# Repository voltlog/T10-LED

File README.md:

# T10-LED
T10 Automotive LED bulb, based on Cree LEDs and a constant current driver

More info about this project in [Voltlog #319](https://www.youtube.com/watch?v=uEePdwpdCJc).
You can also check out the C5W LED bulb project in [Voltlog #333](https://youtu.be/id2jNSogrME).

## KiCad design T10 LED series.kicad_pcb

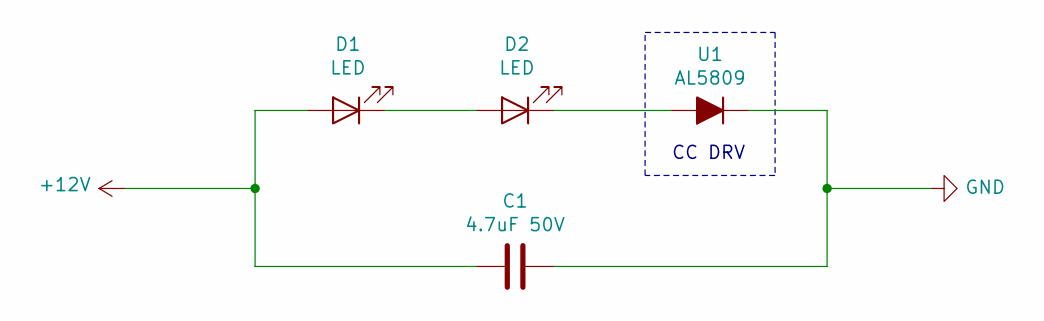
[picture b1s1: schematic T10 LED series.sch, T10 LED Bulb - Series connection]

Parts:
C1: 4.7uF 50V; C_1206_3216Metric; Part Number GCJ31CC71H475KA01L
D1, D2: LED; LED_PLCC_2835
U1: AL5809; D_PowerDI-123

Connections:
+12V: C1.1, D1.2 (A)
GND: C1.2, U1.1 (K)
unnamed: D1.1 (K), D2.2 (A)
unnamed: D2.1 (K), U1.2 (A)

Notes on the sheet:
CC DRV

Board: 2 copper layers, 4 parts (2 on the bottom side), 4 nets, no tracks yet.

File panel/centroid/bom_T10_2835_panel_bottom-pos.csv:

Ref,Val,Package,PosX,PosY,Rot,Side
"D2","LED","LED_PLCC_2835",109.150000,-54.400000,270.000000,bottom
"D2","LED","LED_PLCC_2835",96.250000,-81.400000,270.000000,bottom
"D2","LED","LED_PLCC_2835",134.950000,-81.400000,270.000000,bottom
"D2","LED","LED_PLCC_2835",147.850000,-81.400000,270.000000,bottom
"D2","LED","LED_PLCC_2835",160.750000,-81.400000,270.000000,bottom
"D2","LED","LED_PLCC_2835",173.650000,-81.400000,270.000000,bottom
"D2","LED","LED_PLCC_2835",109.150000,-81.400000,270.000000,bottom
"D2","LED","LED_PLCC_2835",122.050000,-81.400000,270.000000,bottom
"D2","LED","LED_PLCC_2835",173.650000,-54.400000,270.000000,bottom
"D2","LED","LED_PLCC_2835",160.750000,-54.400000,270.000000,bottom
"D2","LED","LED_PLCC_2835",147.850000,-54.400000,270.000000,bottom
"D2","LED","LED_PLCC_2835",134.950000,-54.400000,270.000000,bottom
"D2","LED","LED_PLCC_2835",122.050000,-54.400000,270.000000,bottom
"D2","LED","LED_PLCC_2835",96.250000,-108.400000,270.000000,bottom
"D2","LED","LED_PLCC_2835",160.750000,-108.400000,270.000000,bottom
"D2","LED","LED_PLCC_2835",147.850000,-108.400000,270.000000,bottom
"D2","LED","LED_PLCC_2835",173.650000,-108.400000,270.000000,bottom
"D2","LED","LED_PLCC_2835",109.150000,-108.400000,270.000000,bottom
"D2","LED","LED_PLCC_2835",122.050000,-108.400000,270.000000,bottom
"D2","LED","LED_PLCC_2835",134.950000,-108.400000,270.000000,bottom
"D2","LED","LED_PLCC_2835",96.250000,-54.400000,270.000000,bottom
"REF**","Fiducial_0.75mm_Mask1.5mm","Fiducial_0.75mm_Mask1.5mm",171.000000,-133.900000,180.000000,bottom
"REF**","Fiducial_0.75mm_Mask1.5mm","Fiducial_0.75mm_Mask1.5mm",86.500000,-65.400000,90.000000,bottom
"REF**","Fiducial_0.75mm_Mask1.5mm","Fiducial_0.75mm_Mask1.5mm",167.000000,-42.900000,0.000000,bottom
"U1","AL5809","D_PowerDI-123",147.850000,-63.400000,180.000000,bottom
"U1","AL5809","D_PowerDI-123",134.950000,-63.400000,180.000000,bottom
"U1","AL5809","D_PowerDI-123",96.250000,-63.400000,180.000000,bottom
"U1","AL5809","D_PowerDI-123",122.050000,-63.400000,180.000000,bottom
"U1","AL5809","D_PowerDI-123",109.150000,-63.400000,180.000000,bottom
"U1","AL5809","D_PowerDI-123",147.850000,-117.400000,180.000000,bottom
"U1","AL5809","D_PowerDI-123",160.750000,-63.400000,180.000000,bottom
"U1","AL5809","D_PowerDI-123",173.650000,-63.400000,180.000000,bottom
"U1","AL5809","D_PowerDI-123",96.250000,-90.400000,180.000000,bottom
"U1","AL5809","D_PowerDI-123",122.050000,-90.400000,180.000000,bottom
"U1","AL5809","D_PowerDI-123",160.750000,-90.400000,180.000000,bottom
"U1","AL5809","D_PowerDI-123",173.650000,-90.400000,180.000000,bottom
"U1","AL5809","D_PowerDI-123",134.950000,-90.400000,180.000000,bottom
"U1","AL5809","D_PowerDI-123",147.850000,-90.400000,180.000000,bottom
"U1","AL5809","D_PowerDI-123",109.150000,-90.400000,180.000000,bottom
"U1","AL5809","D_PowerDI-123",96.250000,-117.400000,180.000000,bottom
"U1","AL5809","D_PowerDI-123",122.050000,-117.400000,180.000000,bottom
"U1","AL5809","D_PowerDI-123",160.750000,-117.400000,180.000000,bottom
"U1","AL5809","D_PowerDI-123",173.650000,-117.400000,180.000000,bottom
"U1","AL5809","D_PowerDI-123",134.950000,-117.400000,180.000000,bottom
"U1","AL5809","D_PowerDI-123",109.150000,-117.400000,180.000000,bottom

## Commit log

2020-07-03 Initial commit.
